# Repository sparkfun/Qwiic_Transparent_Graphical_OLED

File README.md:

SparkFun Transparent Graphical OLED Breakout (Qwiic)
========================================

[*SparkFun Transparent Graphical OLED Breakout (Qwiic) (15173)*](https://www.sparkfun.com/products/15173)

The future is here! You asked and we delivered - our Qwiic Transparent Graphical OLED Breakout allows you to display custom images on a transparent screen using either SPI or I<sup>2</sup>C connections. 

With Qwiic connectors it's quick (ha ha) and easy to get started with your own images. However, we still have broken out 0.1"-spaced pins in case you prefer to use a breadboard. Brilliantly lit in the dark and still visible by daylight, this OLED sports a display area of 128x64 pixels, 128x56 of which are completely transparent. Control of the OLED is based on our new HyperDisplay library. 

The Arduino sketch required to drive this display requires quite a bit of dynamic memory, meaning that it is not going to fit on a smaller controller like an ATmega328. Any controller with larger RAM should have no problem. In addition, your 3.3v source should be robust enough to supply around 400mA to the display.

Repository Contents
-------------------

* **/Documentation** - Data sheets, additional product information
* **/Hardware** - Eagle design files (.brd, .sch)
* **/Software** - Related software for the <PRODUCT NAME>

Documentation
--------------
* **[Hookup Guide](https://learn.sparkfun.com/tutorials/transparent-graphical-oled-breakout-hookup-guide)** - Basic hookup guide for the Transparent Graphical OLED.
* **[HyperDisplay Library](https://github.com/sparkfun/SparkFun_HyperDisplay)** - Base arduino library for HyperDisplay.
* **[HyperDisplay SSD1309 Arduino Library](https://github.com/sparkfun/HyperDisplay_SSD1309_ArduinoLibrary)** - Standardized library for control of displays using the SSD1309 driver IC.
* **[HyperDisplay Transparent Graphical OLED Library (UG2856KLBAG01)](https://github.com/sparkfun/HyperDisplay_UG2856KLBAG01_ArduinoLibrary)** - Arduino Library specific to this graphical display
* **[SparkFun Fritzing repo](https://github.com/sparkfun/Fritzing_Parts)** - Fritzing diagrams for SparkFun products. 

License Information
-------------------

This product is _**open source**_! 

Please review the LICENSE.md file for license information. 

If you have any questions or concerns on licensing, please contact techsupport@sparkfun.com.

Distributed as-is; no warranty is given.

- Your friends at SparkFun.

_<COLLABORATION CREDIT>_

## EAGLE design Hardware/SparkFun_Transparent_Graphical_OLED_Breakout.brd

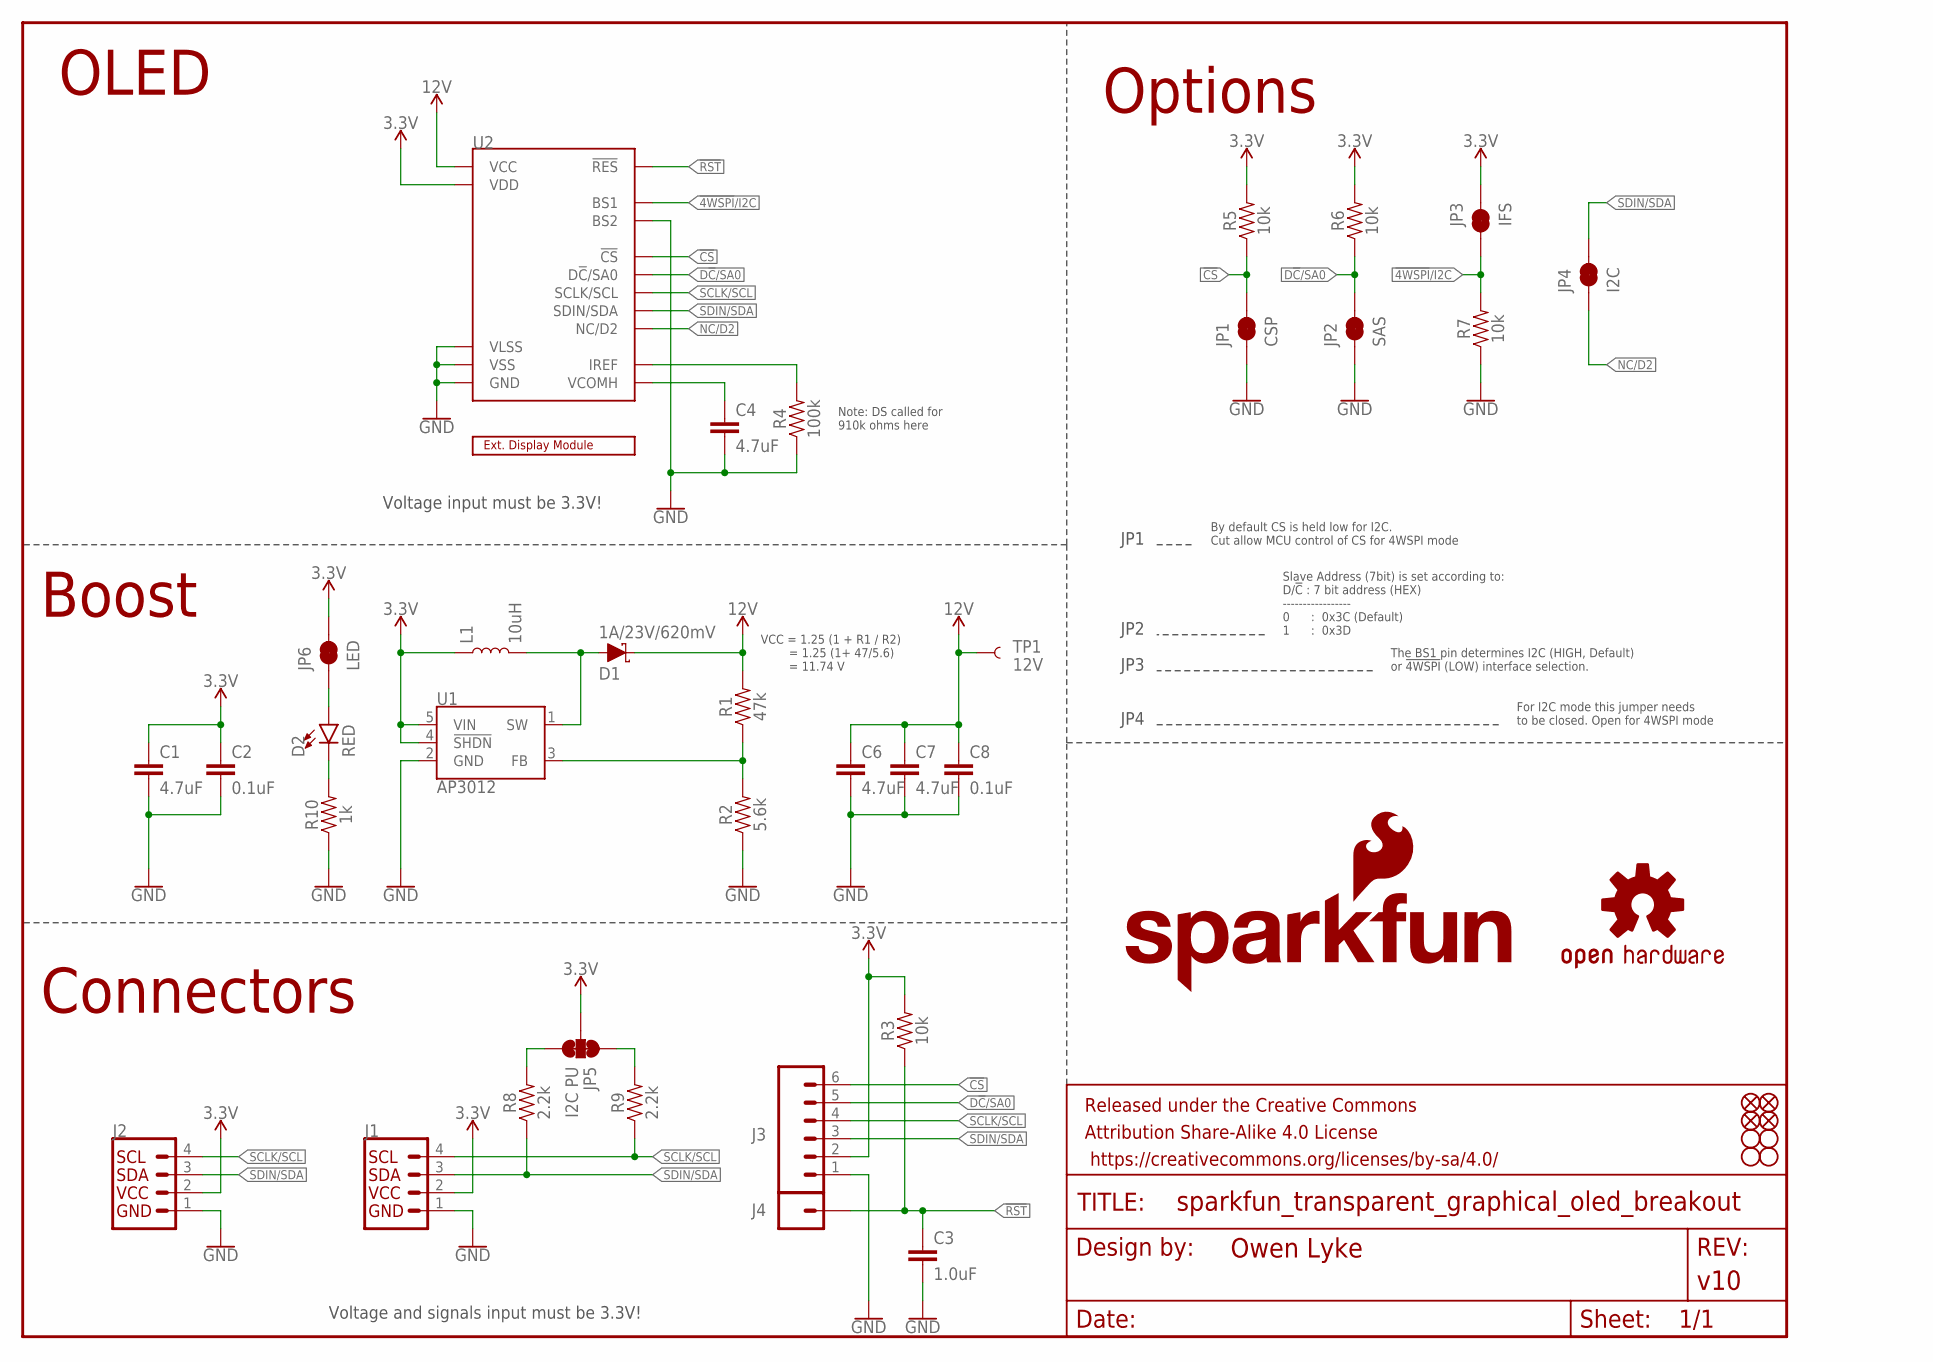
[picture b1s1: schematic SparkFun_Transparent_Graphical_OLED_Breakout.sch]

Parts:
C1, C4, C6, C7: 4.7uF; 0603
C2, C8: 0.1uF; 0603
C3: 1.0uF; 0603
D1: 1A/23V/620mV; SOD-323
D2: RED; LED-0603
FD1, FD2, FD3, FD4: FIDUCIAL1X2; FIDUCIAL-1X2
FRAME1: FRAME-LETTER; CREATIVE_COMMONS
H1, H2, H3, H4: STAND-OFF
J1, J2: QWIIC_CONNECTORJS-1MM; JST04_1MM_RA
J3: CONN_06NO_SILK_NO_POP; 1X06_NO_SILK
J4: CONN_01PTH_NO_SILK_YES_STOP; 1X01_NO_SILK
JP1: CSP; SMT-JUMPER_2_NC_TRACE_SILK
JP2: SAS; SMT-JUMPER_2_NC_TRACE_SILK
JP3: IFS; SMT-JUMPER_2_NC_TRACE_SILK
JP4: I2C; SMT-JUMPER_2_NC_TRACE_SILK
JP5: I2C PU; SMT-JUMPER_3_2-NC_TRACE_SILK
JP6: LED; SMT-JUMPER_2_NC_TRACE_SILK
L1: 10uH; INDUCTOR_4.7UH
LOGO1: SFE_LOGO_NAME_FLAME.1_INCH; SFE_LOGO_NAME_FLAME_.1
LOGO2: OSHW-LOGOS; OSHW-LOGO-S
R1: 47k; 0603
R2: 5.6k; 0603
R3, R5, R6, R7: 10k; 0603
R4: 100k; 0603
R8, R9: 2.2k; 0603
R10: 1k; 0603
TP1: 12V; PAD.03X.03
U1: AP3012; SOT23-5
U2: UG-2856KLBAG01_4WSPI; FPC05024-42201
U$26: EXTERNAL_DISP-UG-2856KLBAG01; EXT_DISP

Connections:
3.3V: C1.1, C2.1, J1.2, J2.2, J3.2, JP3.1, JP5.2, JP6.2, L1.P$1 (1), R3.2, R5.2, R6.2, U1.4 (!SHDN!), U1.5 (VIN), U2.P$5 (VDD)
12V: C6.1, C7.1, C8.1, D1.C, R1.2, TP1.P$1, U2.P$23 (VCC)
!4WSPI!/I2C: JP3.2, R7.2, U2.P$6 (BS1)
!CS: J3.6, JP1.2, R5.1, U2.P$8 (!CS)
!RST: C3.1, J4.1, R3.1, U2.P$9 (!RES)
D!C!/SA0: J3.5, JP2.2, R6.1, U2.P$10 (D!C!/SA0)
GND: C1.2, C2.2, C3.2, C4.2, C6.2, C7.2, C8.2, J1.1, J2.1, J3.1, JP1.1, JP2.1, R2.1, R4.1, R7.1, R10.1, U1.2 (GND), U2.P$1 (GND), U2.P$2 (VLSS), U2.P$3 (VSS), U2.P$7 (BS2), U2.P$11 (GND), U2.P$12 (GND), U2.P$16 (GND), U2.P$17 (GND), U2.P$18 (GND), U2.P$19 (GND), U2.P$20 (GND), U2.P$24 (GND)
unnamed: R4.2, U2.P$21 (IREF)
unnamed: D2.C, R10.2
unnamed: C4.1, U2.P$22 (VCOMH)
unnamed: D1.A, L1.P$2 (2), U1.1 (SW)
unnamed: R1.1, R2.2, U1.3 (FB)
unnamed: JP5.3, R8.2
unnamed: JP5.1, R9.2
unnamed: D2.A, JP6.1
NC/D2: JP4.1, U2.P$15 (NC/D2)
SCLK/SCL: J1.4, J2.4, J3.4, R9.1, U2.P$13 (SCLK/SCL)
SDIN/SDA: J1.3, J2.3, J3.3, JP4.2, R8.1, U2.P$14 (SDIN/SDA)

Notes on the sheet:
Note: DS called for 910k ohms here
VCC = 1.25 (1 + R1 / R2) = 1.25 (1+ 47/5.6) = 11.74 V
By default CS is held low for I2C. Cut allow MCU control of CS for 4WSPI mode
Slave Address (7bit) is set according to: D/!C! : 7 bit address (HEX) ----------------- 0 : 0x3C (Default) 1 : 0x3D
The BS1 pin determines I2C (HIGH, Default) or !4WSPI! (LOW) interface selection.
For I2C mode this jumper needs to be closed. Open for 4WSPI mode
Connectors
Boost
OLED
Options
Voltage input must be 3.3V!
Voltage and signals input must be 3.3V!
JP1
JP2
JP3
JP4

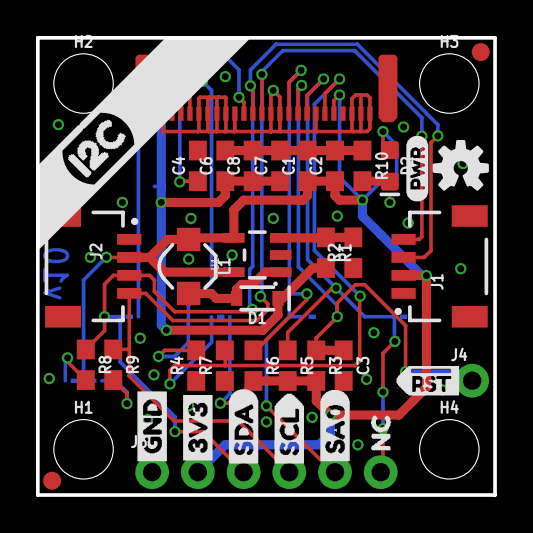
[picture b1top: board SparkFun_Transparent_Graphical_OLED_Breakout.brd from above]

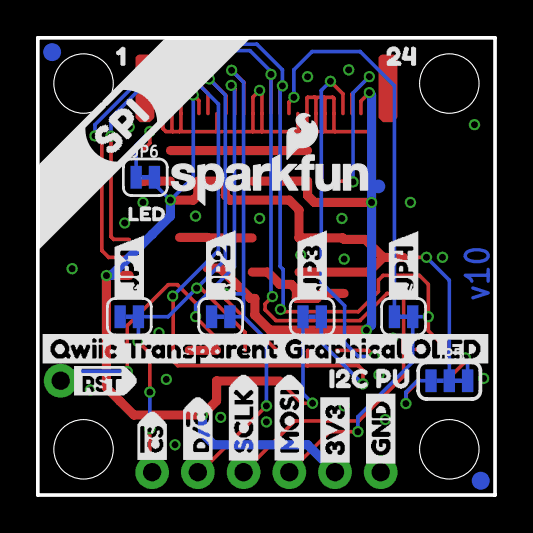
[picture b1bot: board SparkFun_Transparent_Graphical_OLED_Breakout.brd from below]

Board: 2 copper layers, 25.4 x 25.4 mm, 71 parts (27 on the bottom side), 18 nets.

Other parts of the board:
U$1: JP10
U$2: QWIIC_TRANSPARENT_GRAPHICAL_OLED15
U$3: JP21
U$4, U$14: GND0
U$5, U$13: 3V31
U$6: SCL0
U$7: SDA3
U$8: #CS7
U$9: NC10
U$10: MOSI9
U$11: JP32
U$12: SA08
U$15: D##C6
U$16: JP43
U$17: #RST1
U$18: LED4
U$19: I2C3
U$20: SCLK2
U$21: PWR5
U$22: 17
U$23: 248
U$24: SPI2
U$25: I2C_PU0
U$28: #RST0

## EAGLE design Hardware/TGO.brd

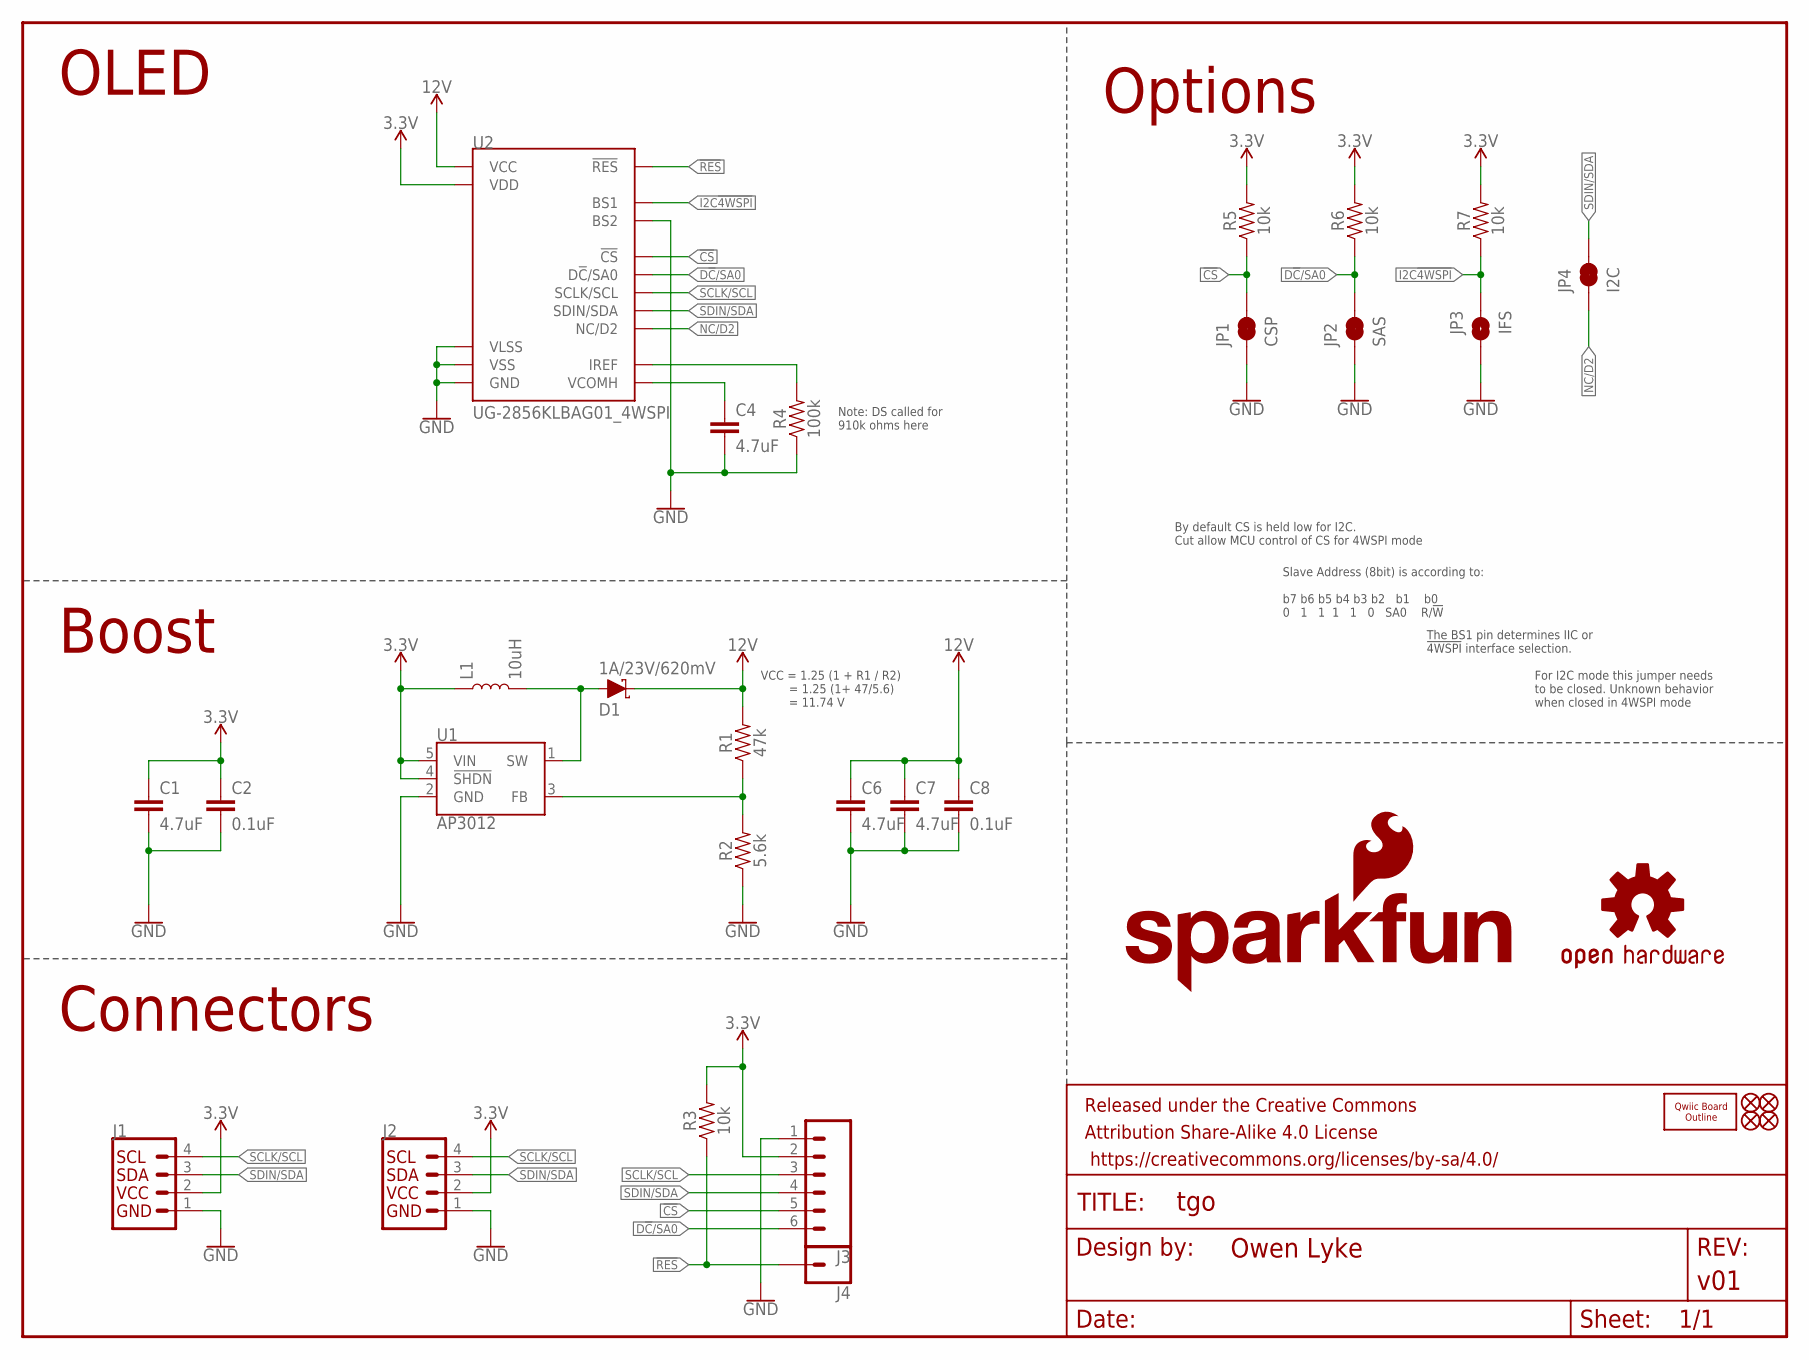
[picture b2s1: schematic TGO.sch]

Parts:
C1, C4, C6, C7: 4.7uF; 0603
C2, C8: 0.1uF; 0603
D1: 1A/23V/620mV; SOD-323
FD1, FD2, FD3, FD4: FIDUCIAL1X2; FIDUCIAL-1X2
FRAME1: FRAME-LETTER; CREATIVE_COMMONS
J1, J2: QWIIC_CONNECTORJS-1MM; 1X04_1MM_RA
J3: CONN_06NO_SILK_NO_POP; 1X06_NO_SILK
J4: CONN_01PTH_NO_SILK_YES_STOP; 1X01_NO_SILK
JP1: CSP; SMT-JUMPER_2_NC_TRACE_SILK
JP2: SAS; SMT-JUMPER_2_NC_TRACE_SILK
JP3: IFS; SMT-JUMPER_2_NO_SILK
JP4: I2C; SMT-JUMPER_2_NC_TRACE_SILK
L1: 10uH; INDUCTOR_4.7UH
LOGO1: SFE_LOGO_NAME_FLAME.1_INCH; SFE_LOGO_NAME_FLAME_.1
LOGO2: OSHW-LOGOS; OSHW-LOGO-S
R1: 47k; 0603
R2: 5.6k; 0603
R3, R5, R6, R7: 10k; 0603
R4: 100k; 0603
U1: AP3012; SOT23-5
U2: UG-2856KLBAG01_4WSPI; FPC05024-42201
U$1: QWIIC_BOARD_OUTLINEH; QWIIC_BOARD_MOUNT_HOLES

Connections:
3.3V: C1.1, C2.1, J1.2, J2.2, J3.2, L1.P$1 (1), R3.2, R5.2, R6.2, R7.2, U1.4 (!SHDN!), U1.5 (VIN), U2.P$5 (VDD)
12V: C6.1, C7.1, C8.1, D1.C, R1.2, U2.P$23 (VCC)
!CS: J3.5, JP1.2, R5.1, U2.P$8 (!CS)
!RES: J4.1, R3.1, U2.P$9 (!RES)
D!C!/SA0: J3.6, JP2.2, R6.1, U2.P$10 (D!C!/SA0)
GND: C1.2, C2.2, C4.2, C6.2, C7.2, C8.2, J1.1, J2.1, J3.1, JP1.1, JP2.1, JP3.2, R2.1, R4.1, U1.2 (GND), U2.P$1 (GND), U2.P$2 (VLSS), U2.P$3 (VSS), U2.P$7 (BS2), U2.P$11 (GND), U2.P$12 (GND), U2.P$16 (GND), U2.P$17 (GND), U2.P$18 (GND), U2.P$19 (GND), U2.P$20 (GND), U2.P$24 (GND)
I2C!4WSPI: JP3.1, R7.1, U2.P$6 (BS1)
unnamed: R4.2, U2.P$21 (IREF)
unnamed: C4.1, U2.P$22 (VCOMH)
unnamed: D1.A, L1.P$2 (2), U1.1 (SW)
unnamed: R1.1, R2.2, U1.3 (FB)
NC/D2: JP4.1, U2.P$15 (NC/D2)
SCLK/SCL: J1.4, J2.4, J3.3, U2.P$13 (SCLK/SCL)
SDIN/SDA: J1.3, J2.3, J3.4, JP4.2, U2.P$14 (SDIN/SDA)

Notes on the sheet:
Note: DS called for 910k ohms here
VCC = 1.25 (1 + R1 / R2) = 1.25 (1+ 47/5.6) = 11.74 V
By default CS is held low for I2C. Cut allow MCU control of CS for 4WSPI mode
Slave Address (8bit) is according to: b7 b6 b5 b4 b3 b2 b1 b0 0 1 1 1 1 0 SA0 R/!W
The BS1 pin determines IIC or !4WSPI! interface selection.
For I2C mode this jumper needs to be closed. Unknown behavior when closed in 4WSPI mode
Connectors
Boost
OLED
Options

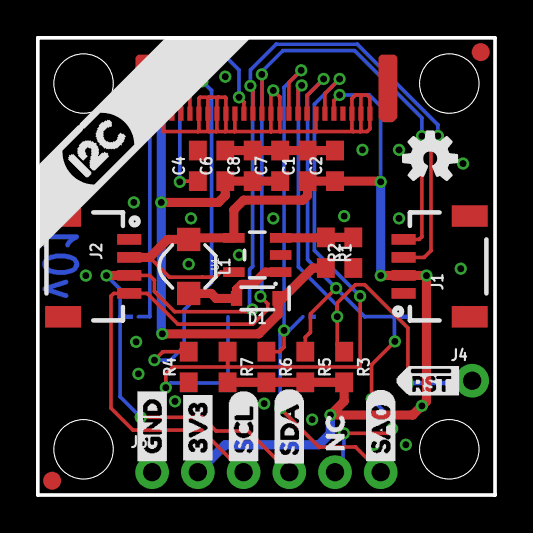
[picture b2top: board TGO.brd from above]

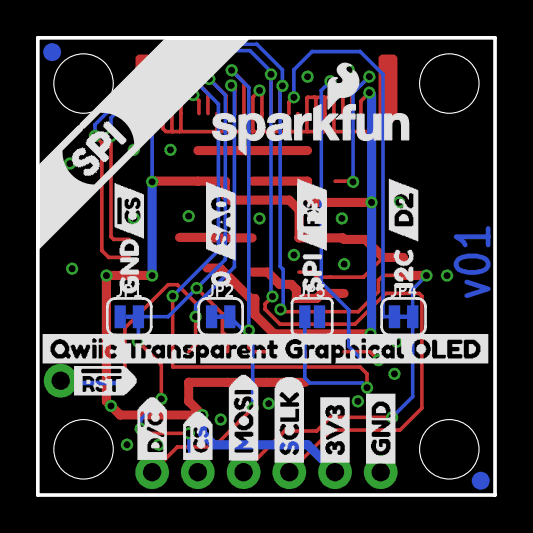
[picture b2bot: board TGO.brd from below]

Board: 2 copper layers, 25.4 x 25.4 mm, 59 parts (25 on the bottom side), 14 nets.

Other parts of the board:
U$2: QWIIC_TRANSPARENT_GRAPHICAL_OLED15
U$3, U$20: D27
U$4, U$14: GND0
U$5, U$13: 3V31
U$6: SCL2
U$7: SDA3
U$8: #CS7
U$9: NC10
U$10: MOSI9
U$11: SCLK8
U$12: SA08
U$15: D##C6
U$16: GND10
U$17: #RST1
U$18: 013
U$19: I2C3
U$21: SA05
U$22: I2C13
U$23: #CS4
U$24: SPI2
U$26: IFS17
U$28: #RST0
U$29: SPI6

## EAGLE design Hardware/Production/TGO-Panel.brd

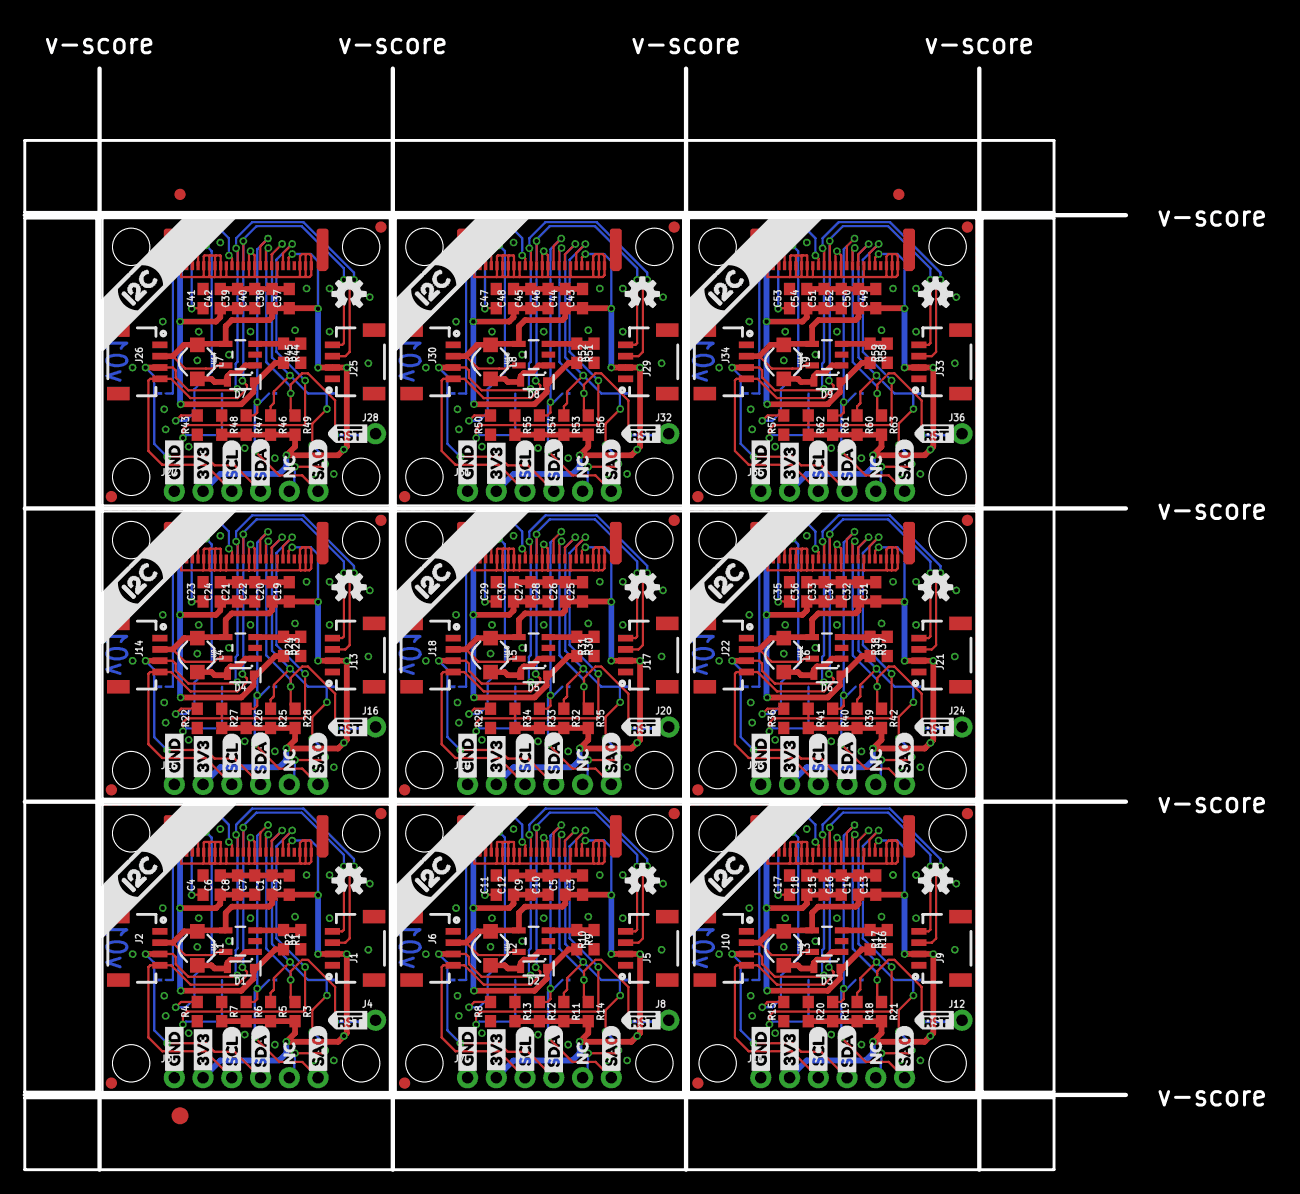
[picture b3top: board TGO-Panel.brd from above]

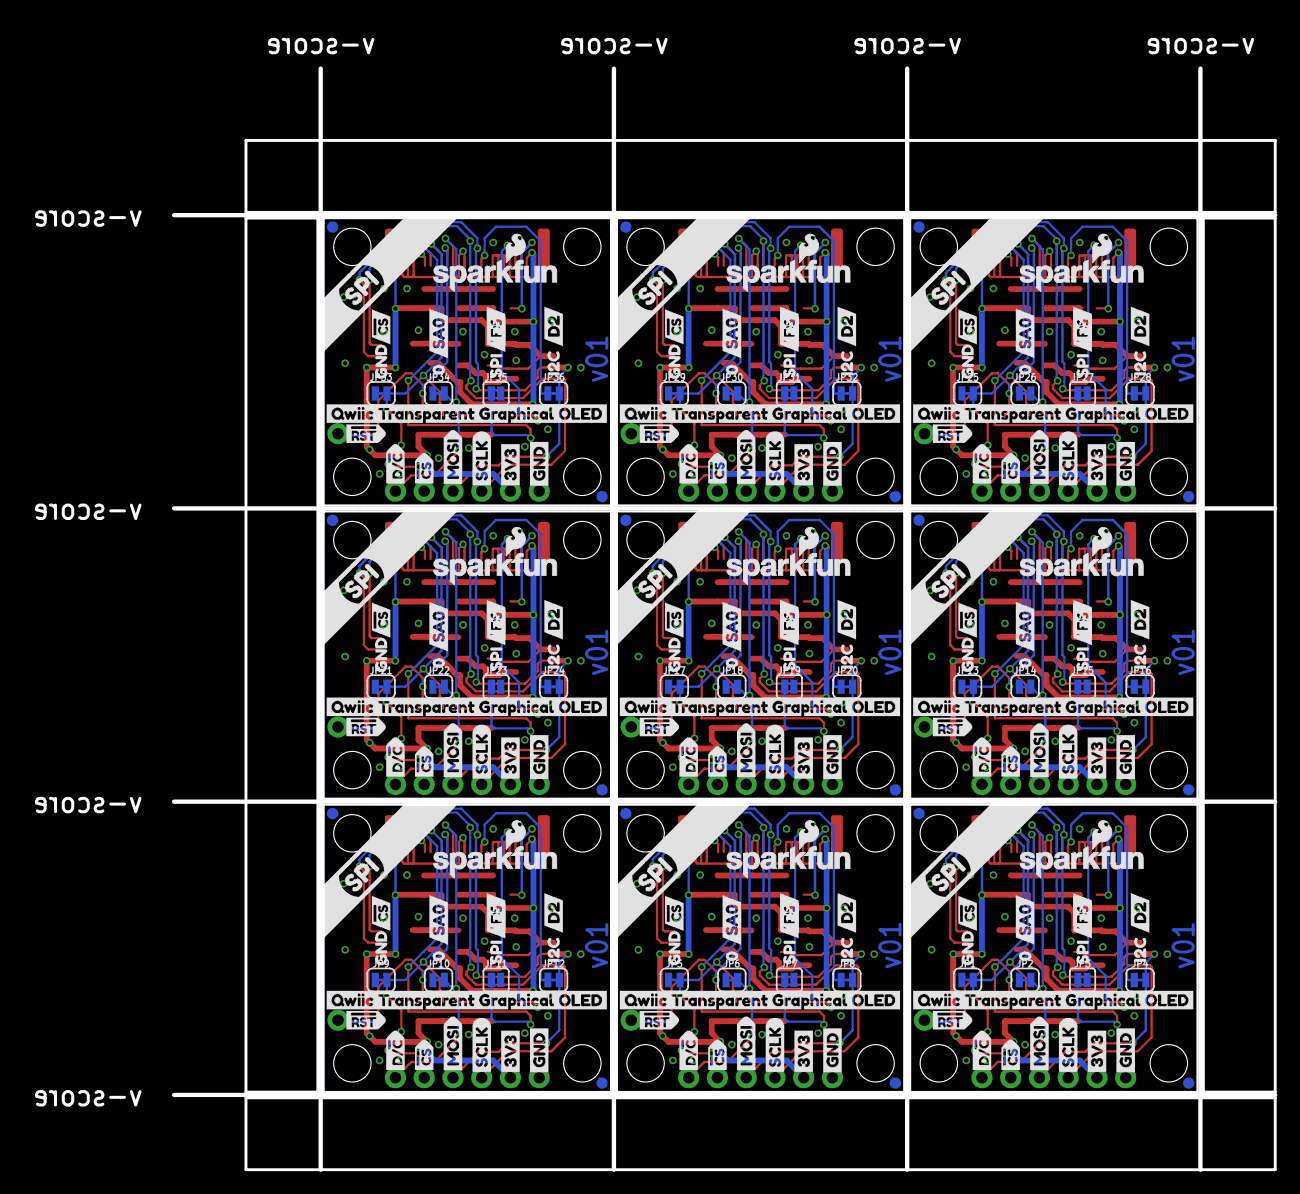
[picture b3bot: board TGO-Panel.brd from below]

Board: 2 copper layers, 110.5 x 101.2 mm, 525 parts (225 on the bottom side), 126 nets.

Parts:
C1, C4, C5, C6, C7, C10, C11, C12, C14, C16, C17, C18, C20, C22, C23, C24, C26, C28, C29, C30, C32, C34, C35, C36, C38, C40, C41, C42, C44, C46, C47, C48, C50, C52, C53, C54: 4.7uF; 0603
C2, C3, C8, C9, C13, C15, C19, C21, C25, C27, C31, C33, C37, C39, C43, C45, C49, C51: 0.1uF; 0603
D1, D2, D3, D4, D5, D6, D7, D8, D9: 1A/23V/620mV; SOD-323
E$1, E$2: FIDUCIAL-1X2
E$3: FIDUCIAL-1.5X3
FD1, FD2, FD3, FD4, FD5, FD6, FD7, FD8, FD9, FD10, FD11, FD12, FD13, FD14, FD15, FD16, FD17, FD18, FD19, FD20, FD21, FD22, FD23, FD24, FD25, FD26, FD27, FD28, FD29, FD30, FD31, FD32, FD33, FD34, FD35, FD36: FIDUCIAL1X2; FIDUCIAL-1X2
J1, J2, J5, J6, J9, J10, J13, J14, J17, J18, J21, J22, J25, J26, J29, J30, J33, J34: 1X04_1MM_RA
J3, J7, J11, J15, J19, J23, J27, J31, J35: 1X06_NO_SILK
J4, J8, J12, J16, J20, J24, J28, J32, J36: 1X01_NO_SILK
JP1, JP5, JP9, JP13, JP17, JP21, JP25, JP29, JP33: CSP; SMT-JUMPER_2_NC_TRACE_SILK
JP2, JP6, JP10, JP14, JP18, JP22, JP26, JP30, JP34: SAS; SMT-JUMPER_2_NC_TRACE_SILK
JP3, JP7, JP11, JP15, JP19, JP23, JP27, JP31, JP35: IFS; SMT-JUMPER_2_NO_SILK
JP4, JP8, JP12, JP16, JP20, JP24, JP28, JP32, JP36: I2C; SMT-JUMPER_2_NC_TRACE_SILK
L1, L2, L3, L4, L5, L6, L7, L8, L9: 10uH; INDUCTOR_4.7UH
LOGO1, LOGO4, LOGO6, LOGO8, LOGO10, LOGO12, LOGO14, LOGO16, LOGO18: SFE_LOGO_NAME_FLAME.1_INCH; SFE_LOGO_NAME_FLAME_.1
LOGO2, LOGO3, LOGO5, LOGO7, LOGO9, LOGO11, LOGO13, LOGO15, LOGO17: OSHW-LOGOS; OSHW-LOGO-S
R1, R9, R16, R23, R30, R37, R44, R51, R58: 47k; 0603
R2, R10, R17, R24, R31, R38, R45, R52, R59: 5.6k; 0603
R3, R5, R6, R7, R11, R12, R13, R14, R18, R19, R20, R21, R25, R26, R27, R28, R32, R33, R34, R35, R39, R40, R41, R42, R46, R47, R48, R49, R53, R54, R55, R56, R60, R61, R62, R63: 10k; 0603
R4, R8, R15, R22, R29, R36, R43, R50, R57: 100k; 0603
U1, U4, U6, U8, U10, U12, U14, U16, U18: AP3012; SOT23-5
U2, U3, U5, U7, U9, U11, U13, U15, U17: SAS1-1U001-A_I2C_4WSPI; FPC05024-42201
U$1, U$25, U$55, U$82, U$109, U$136, U$163, U$190, U$217: QWIIC_BOARD_OUTLINEH; QWIIC_BOARD_MOUNT_HOLES
U$2, U$44, U$71, U$98, U$125, U$152, U$179, U$206, U$233: QWIIC_TRANSPARENT_GRAPHICAL_OLED15
U$3, U$20, U$53, U$54, U$80, U$81, U$107, U$108, U$134, U$135, U$161, U$162, U$188, U$189, U$215, U$216, U$242, U$243: D27
U$4, U$14, U$27, U$39, U$56, U$66, U$83, U$93, U$110, U$120, U$137, U$147, U$164, U$174, U$191, U$201, U$218, U$228: GND0
U$5, U$13, U$30, U$38, U$57, U$65, U$84, U$92, U$111, U$119, U$138, U$146, U$165, U$173, U$192, U$200, U$219, U$227: 3V31
U$6, U$31, U$58, U$85, U$112, U$139, U$166, U$193, U$220: SCL2
U$7, U$32, U$59, U$86, U$113, U$140, U$167, U$194, U$221: SDA3
U$8, U$35, U$62, U$89, U$116, U$143, U$170, U$197, U$224: #CS7
U$9, U$34, U$61, U$88, U$115, U$142, U$169, U$196, U$223: NC10
U$10, U$36, U$63, U$90, U$117, U$144, U$171, U$198, U$225: MOSI9
U$11, U$37, U$64, U$91, U$118, U$145, U$172, U$199, U$226: SCLK8
U$12, U$33, U$60, U$87, U$114, U$141, U$168, U$195, U$222: SA08
U$15, U$40, U$67, U$94, U$121, U$148, U$175, U$202, U$229: D##C6
U$16, U$41, U$68, U$95, U$122, U$149, U$176, U$203, U$230: GND10
U$17, U$47, U$74, U$101, U$128, U$155, U$182, U$209, U$236: #RST1
U$18, U$42, U$69, U$96, U$123, U$150, U$177, U$204, U$231: 013
U$19, U$48, U$75, U$102, U$129, U$156, U$183, U$210, U$237: I2C3
U$21, U$50, U$77, U$104, U$131, U$158, U$185, U$212, U$239: SA05
U$22, U$43, U$70, U$97, U$124, U$151, U$178, U$205, U$232: I2C13
U$23, U$51, U$78, U$105, U$132, U$159, U$186, U$213, U$240: #CS4
U$24, U$49, U$76, U$103, U$130, U$157, U$184, U$211, U$238: SPI2
U$26, U$45, U$72, U$99, U$126, U$153, U$180, U$207, U$234: IFS17
U$28, U$46, U$73, U$100, U$127, U$154, U$181, U$208, U$235: #RST0
U$29, U$52, U$79, U$106, U$133, U$160, U$187, U$214, U$241: SPI6

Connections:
3.3V: C1.1, C2.1, J1.2, J2.2, J3.2, L1.P$1, R3.2, R5.2, R6.2, R7.2, U1.4, U1.5, U2.P$5
3.3V1: C3.1, C5.1, J5.2, J6.2, J7.2, L2.P$1, R11.2, R12.2, R13.2, R14.2, U3.P$5, U4.4, U4.5
3.3V2: C13.1, C14.1, J9.2, J10.2, J11.2, L3.P$1, R18.2, R19.2, R20.2, R21.2, U5.P$5, U6.4, U6.5
3.3V3: C19.1, C20.1, J13.2, J14.2, J15.2, L4.P$1, R25.2, R26.2, R27.2, R28.2, U7.P$5, U8.4, U8.5
3.3V4: C25.1, C26.1, J17.2, J18.2, J19.2, L5.P$1, R32.2, R33.2, R34.2, R35.2, U9.P$5, U10.4, U10.5
3.3V5: C31.1, C32.1, J21.2, J22.2, J23.2, L6.P$1, R39.2, R40.2, R41.2, R42.2, U11.P$5, U12.4, U12.5
3.3V6: C37.1, C38.1, J25.2, J26.2, J27.2, L7.P$1, R46.2, R47.2, R48.2, R49.2, U13.P$5, U14.4, U14.5
3.3V7: C43.1, C44.1, J29.2, J30.2, J31.2, L8.P$1, R53.2, R54.2, R55.2, R56.2, U15.P$5, U16.4, U16.5
3.3V8: C49.1, C50.1, J33.2, J34.2, J35.2, L9.P$1, R60.2, R61.2, R62.2, R63.2, U17.P$5, U18.4, U18.5
12V: C6.1, C7.1, C8.1, D1.C, R1.2, U2.P$23
12V1: C9.1, C10.1, C12.1, D2.C, R9.2, U3.P$23
12V2: C15.1, C16.1, C18.1, D3.C, R16.2, U5.P$23
12V3: C21.1, C22.1, C24.1, D4.C, R23.2, U7.P$23
12V4: C27.1, C28.1, C30.1, D5.C, R30.2, U9.P$23
12V5: C33.1, C34.1, C36.1, D6.C, R37.2, U11.P$23
12V6: C39.1, C40.1, C42.1, D7.C, R44.2, U13.P$23
12V7: C45.1, C46.1, C48.1, D8.C, R51.2, U15.P$23
12V8: C51.1, C52.1, C54.1, D9.C, R58.2, U17.P$23
!CS: J3.5, JP1.2, R5.1, U2.P$8
!CS1: J7.5, JP5.2, R11.1, U3.P$8
!CS2: J11.5, JP9.2, R18.1, U5.P$8
!CS3: J15.5, JP13.2, R25.1, U7.P$8
!CS4: J19.5, JP17.2, R32.1, U9.P$8
!CS5: J23.5, JP21.2, R39.1, U11.P$8
!CS6: J27.5, JP25.2, R46.1, U13.P$8
!CS7: J31.5, JP29.2, R53.1, U15.P$8
!CS8: J35.5, JP33.2, R60.1, U17.P$8
!RES: J4.1, R3.1, U2.P$9
!RES1: J8.1, R14.1, U3.P$9
!RES2: J12.1, R21.1, U5.P$9
!RES3: J16.1, R28.1, U7.P$9
!RES4: J20.1, R35.1, U9.P$9
!RES5: J24.1, R42.1, U11.P$9
!RES6: J28.1, R49.1, U13.P$9
!RES7: J32.1, R56.1, U15.P$9
!RES8: J36.1, R63.1, U17.P$9
D!C!/SA0: J3.6, JP2.2, R6.1, U2.P$10
D!C!/SA1: J7.6, JP6.2, R12.1, U3.P$10
D!C!/SA2: J11.6, JP10.2, R19.1, U5.P$10
D!C!/SA3: J15.6, JP14.2, R26.1, U7.P$10
D!C!/SA4: J19.6, JP18.2, R33.1, U9.P$10
D!C!/SA5: J23.6, JP22.2, R40.1, U11.P$10
D!C!/SA6: J27.6, JP26.2, R47.1, U13.P$10
D!C!/SA7: J31.6, JP30.2, R54.1, U15.P$10
D!C!/SA8: J35.6, JP34.2, R61.1, U17.P$10
GND: C1.2, C2.2, C4.2, C6.2, C7.2, C8.2, J1.1, J2.1, J3.1, JP1.1, JP2.1, JP3.2, R2.1, R4.1, U1.2, U2.P$1, U2.P$2, U2.P$3, U2.P$7, U2.P$11, U2.P$12, U2.P$16, U2.P$17, U2.P$18, U2.P$19, U2.P$20, U2.P$24
GND1: C3.2, C5.2, C9.2, C10.2, C11.2, C12.2, J5.1, J6.1, J7.1, JP5.1, JP6.1, JP7.2, R8.1, R10.1, U3.P$1, U3.P$2, U3.P$3, U3.P$7, U3.P$11, U3.P$12, U3.P$16, U3.P$17, U3.P$18, U3.P$19, U3.P$20, U3.P$24, U4.2
GND2: C13.2, C14.2, C15.2, C16.2, C17.2, C18.2, J9.1, J10.1, J11.1, JP9.1, JP10.1, JP11.2, R15.1, R17.1, U5.P$1, U5.P$2, U5.P$3, U5.P$7, U5.P$11, U5.P$12, U5.P$16, U5.P$17, U5.P$18, U5.P$19, U5.P$20, U5.P$24, U6.2
GND3: C19.2, C20.2, C21.2, C22.2, C23.2, C24.2, J13.1, J14.1, J15.1, JP13.1, JP14.1, JP15.2, R22.1, R24.1, U7.P$1, U7.P$2, U7.P$3, U7.P$7, U7.P$11, U7.P$12, U7.P$16, U7.P$17, U7.P$18, U7.P$19, U7.P$20, U7.P$24, U8.2
GND4: C25.2, C26.2, C27.2, C28.2, C29.2, C30.2, J17.1, J18.1, J19.1, JP17.1, JP18.1, JP19.2, R29.1, R31.1, U9.P$1, U9.P$2, U9.P$3, U9.P$7, U9.P$11, U9.P$12, U9.P$16, U9.P$17, U9.P$18, U9.P$19, U9.P$20, U9.P$24, U10.2
GND5: C31.2, C32.2, C33.2, C34.2, C35.2, C36.2, J21.1, J22.1, J23.1, JP21.1, JP22.1, JP23.2, R36.1, R38.1, U11.P$1, U11.P$2, U11.P$3, U11.P$7, U11.P$11, U11.P$12, U11.P$16, U11.P$17, U11.P$18, U11.P$19, U11.P$20, U11.P$24, U12.2
GND6: C37.2, C38.2, C39.2, C40.2, C41.2, C42.2, J25.1, J26.1, J27.1, JP25.1, JP26.1, JP27.2, R43.1, R45.1, U13.P$1, U13.P$2, U13.P$3, U13.P$7, U13.P$11, U13.P$12, U13.P$16, U13.P$17, U13.P$18, U13.P$19, U13.P$20, U13.P$24, U14.2
GND7: C43.2, C44.2, C45.2, C46.2, C47.2, C48.2, J29.1, J30.1, J31.1, JP29.1, JP30.1, JP31.2, R50.1, R52.1, U15.P$1, U15.P$2, U15.P$3, U15.P$7, U15.P$11, U15.P$12, U15.P$16, U15.P$17, U15.P$18, U15.P$19, U15.P$20, U15.P$24, U16.2
GND8: C49.2, C50.2, C51.2, C52.2, C53.2, C54.2, J33.1, J34.1, J35.1, JP33.1, JP34.1, JP35.2, R57.1, R59.1, U17.P$1, U17.P$2, U17.P$3, U17.P$7, U17.P$11, U17.P$12, U17.P$16, U17.P$17, U17.P$18, U17.P$19, U17.P$20, U17.P$24, U18.2
I2C!4WSPI: JP3.1, R7.1, U2.P$6
I2C!4WSPI1: JP7.1, R13.1, U3.P$6
I2C!4WSPI2: JP11.1, R20.1, U5.P$6
I2C!4WSPI3: JP15.1, R27.1, U7.P$6
I2C!4WSPI4: JP19.1, R34.1, U9.P$6
I2C!4WSPI5: JP23.1, R41.1, U11.P$6
I2C!4WSPI6: JP27.1, R48.1, U13.P$6
I2C!4WSPI7: JP31.1, R55.1, U15.P$6
I2C!4WSPI8: JP35.1, R62.1, U17.P$6
unnamed: R4.2, U2.P$21
unnamed: C11.1, U3.P$22
unnamed: C4.1, U2.P$22
unnamed: D1.A, L1.P$2, U1.1
unnamed: R1.1, R2.2, U1.3
unnamed: R8.2, U3.P$21
unnamed: D2.A, L2.P$2, U4.1
unnamed: R9.1, R10.2, U4.3
unnamed: C17.1, U5.P$22
unnamed: R15.2, U5.P$21
unnamed: D3.A, L3.P$2, U6.1
unnamed: R16.1, R17.2, U6.3
unnamed: C23.1, U7.P$22
unnamed: R22.2, U7.P$21
unnamed: D4.A, L4.P$2, U8.1
unnamed: R23.1, R24.2, U8.3
unnamed: C29.1, U9.P$22
unnamed: R29.2, U9.P$21
unnamed: D5.A, L5.P$2, U10.1
unnamed: R30.1, R31.2, U10.3
unnamed: C35.1, U11.P$22
unnamed: R36.2, U11.P$21
unnamed: D6.A, L6.P$2, U12.1
unnamed: R37.1, R38.2, U12.3
unnamed: C41.1, U13.P$22
unnamed: R43.2, U13.P$21
unnamed: D7.A, L7.P$2, U14.1
unnamed: R44.1, R45.2, U14.3
unnamed: C47.1, U15.P$22
unnamed: R50.2, U15.P$21
unnamed: D8.A, L8.P$2, U16.1
unnamed: R51.1, R52.2, U16.3
unnamed: C53.1, U17.P$22
unnamed: R57.2, U17.P$21
unnamed: D9.A, L9.P$2, U18.1
unnamed: R58.1, R59.2, U18.3
NC/D1: JP8.1, U3.P$15
NC/D2: JP4.1, U2.P$15
NC/D3: JP12.1, U5.P$15
NC/D4: JP16.1, U7.P$15
NC/D5: JP20.1, U9.P$15
NC/D6: JP24.1, U11.P$15
NC/D7: JP28.1, U13.P$15
NC/D8: JP32.1, U15.P$15
NC/D9: JP36.1, U17.P$15
SCLK/SCL: J1.4, J2.4, J3.3, U2.P$13
SCLK/SCL1: J5.4, J6.4, J7.3, U3.P$13
SCLK/SCL2: J9.4, J10.4, J11.3, U5.P$13
SCLK/SCL3: J13.4, J14.4, J15.3, U7.P$13
SCLK/SCL4: J17.4, J18.4, J19.3, U9.P$13
SCLK/SCL5: J21.4, J22.4, J23.3, U11.P$13
SCLK/SCL6: J25.4, J26.4, J27.3, U13.P$13
SCLK/SCL7: J29.4, J30.4, J31.3, U15.P$13
SCLK/SCL8: J33.4, J34.4, J35.3, U17.P$13
SDIN/SDA: J1.3, J2.3, J3.4, JP4.2, U2.P$14
SDIN/SDA1: J5.3, J6.3, J7.4, JP8.2, U3.P$14
SDIN/SDA2: J9.3, J10.3, J11.4, JP12.2, U5.P$14
SDIN/SDA3: J13.3, J14.3, J15.4, JP16.2, U7.P$14
SDIN/SDA4: J17.3, J18.3, J19.4, JP20.2, U9.P$14
SDIN/SDA5: J21.3, J22.3, J23.4, JP24.2, U11.P$14
SDIN/SDA6: J25.3, J26.3, J27.4, JP28.2, U13.P$14
SDIN/SDA7: J29.3, J30.3, J31.4, JP32.2, U15.P$14
SDIN/SDA8: J33.3, J34.3, J35.4, JP36.2, U17.P$14

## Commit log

2018-12-21 Finish prototype v01
2018-12-21 Proto review changes
2019-01-11 Move display into SparkFun library
2019-01-14 Add pullup resistors on I2C lines, increment version number
2019-01-18 Add documentation and example code from WiseChip
2019-01-18 Change hardware filenames
2019-01-18 Add capacitor to reset line for delayed start up!
2019-01-24 Fixed proto issues
    Added I2C pullup resistors and disconnect jumper, added power LED, added reset timing capacitor
2019-01-24 Add label for I2C pullup disconnect jumper
2019-01-24 Tidy schematic
2019-01-25 Changed polarity of IFS jumper so that changing to SPI is all cutting, changed silk to match
2019-01-25 Notes from reds review added in board
    Yeah its not standard, but it worked
2019-01-25 Fixed design review notes
    Jumper labels simplified
    FPC polarity markers added
    version number updated
    I2C resistors moved
    test point added for 12V
    LED disconnect jumper added
2019-01-28 Minor changes from Checklist run-through
2019-01-29 Fix issue #2
    Added units to measures
    Removed unused via on 3.3V line (lower right)
    Widened input 3.3V trace to boost IC to 20 mil
2019-01-31 Fix default label of I2C address in schematic
2019-02-15 Add External Display Indicator to help avoid BOM issues
2019-02-15 Add external display indicator to avoid BOM issues
2019-02-25 Make SPI proof use Arduino SPI library
2019-03-05 Removing empty dirs

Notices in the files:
parts and their libraries:
SparkFun-Capacitors: Licensing: Creative Commons ShareAlike 4.0 International - https://creativecommons.org/licenses/by-sa/4.0
SparkFun-Aesthetics: Released under the Creative Commons Attribution Share-Alike 4.0 License
SparkFun-Aesthetics: https://creativecommons.org/licenses/by-sa/4.0
